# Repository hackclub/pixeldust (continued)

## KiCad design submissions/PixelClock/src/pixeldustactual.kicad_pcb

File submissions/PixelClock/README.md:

---
name: "Hudson Green"
slack_id: "U078RA454JH"
github_handle: "@PythonAtSea"
wokwi: https://wokwi.com/projects/429875870626598913
---

# pixelClock

[https://wokwi.com/projects/429875870626598913](https://wokwi.com/projects/429875870626598913)

⚠️ I would like to solder way more than 50 neopixels and a bunch of caps, so I would need a hotplate.

This is a grid of SK6821MINI leds. It is designed mainly to be used as a clock, but the surrounding leds could also be used for other things, and I'm planning on adding a alarm with a webpage later.

BOM

|   Comment     |   Footprint                                   |   Quantity    |   LCSC        |   Price   |
|---------------|-----------------------------------------------|---------------|---------------|-----------|
|   100nF       |   C_0201_0603Metric_Pad0.64x0.40mm_HandSolder |   133         |   C30926      |   $0.44   |
|   10uF        |   C_1210_3225Metric_Pad1.33x2.70mm_HandSolder |   1           |   C7432790    |   $0.38   |
|               |   XIAO-RP2040-DIP                             |   1		    |               |           |
|   Neopixel    |  	SK6812MINI                                  |   133		    |               |           |

Some images of your design (make sure to include both the PCB and Schematic!):

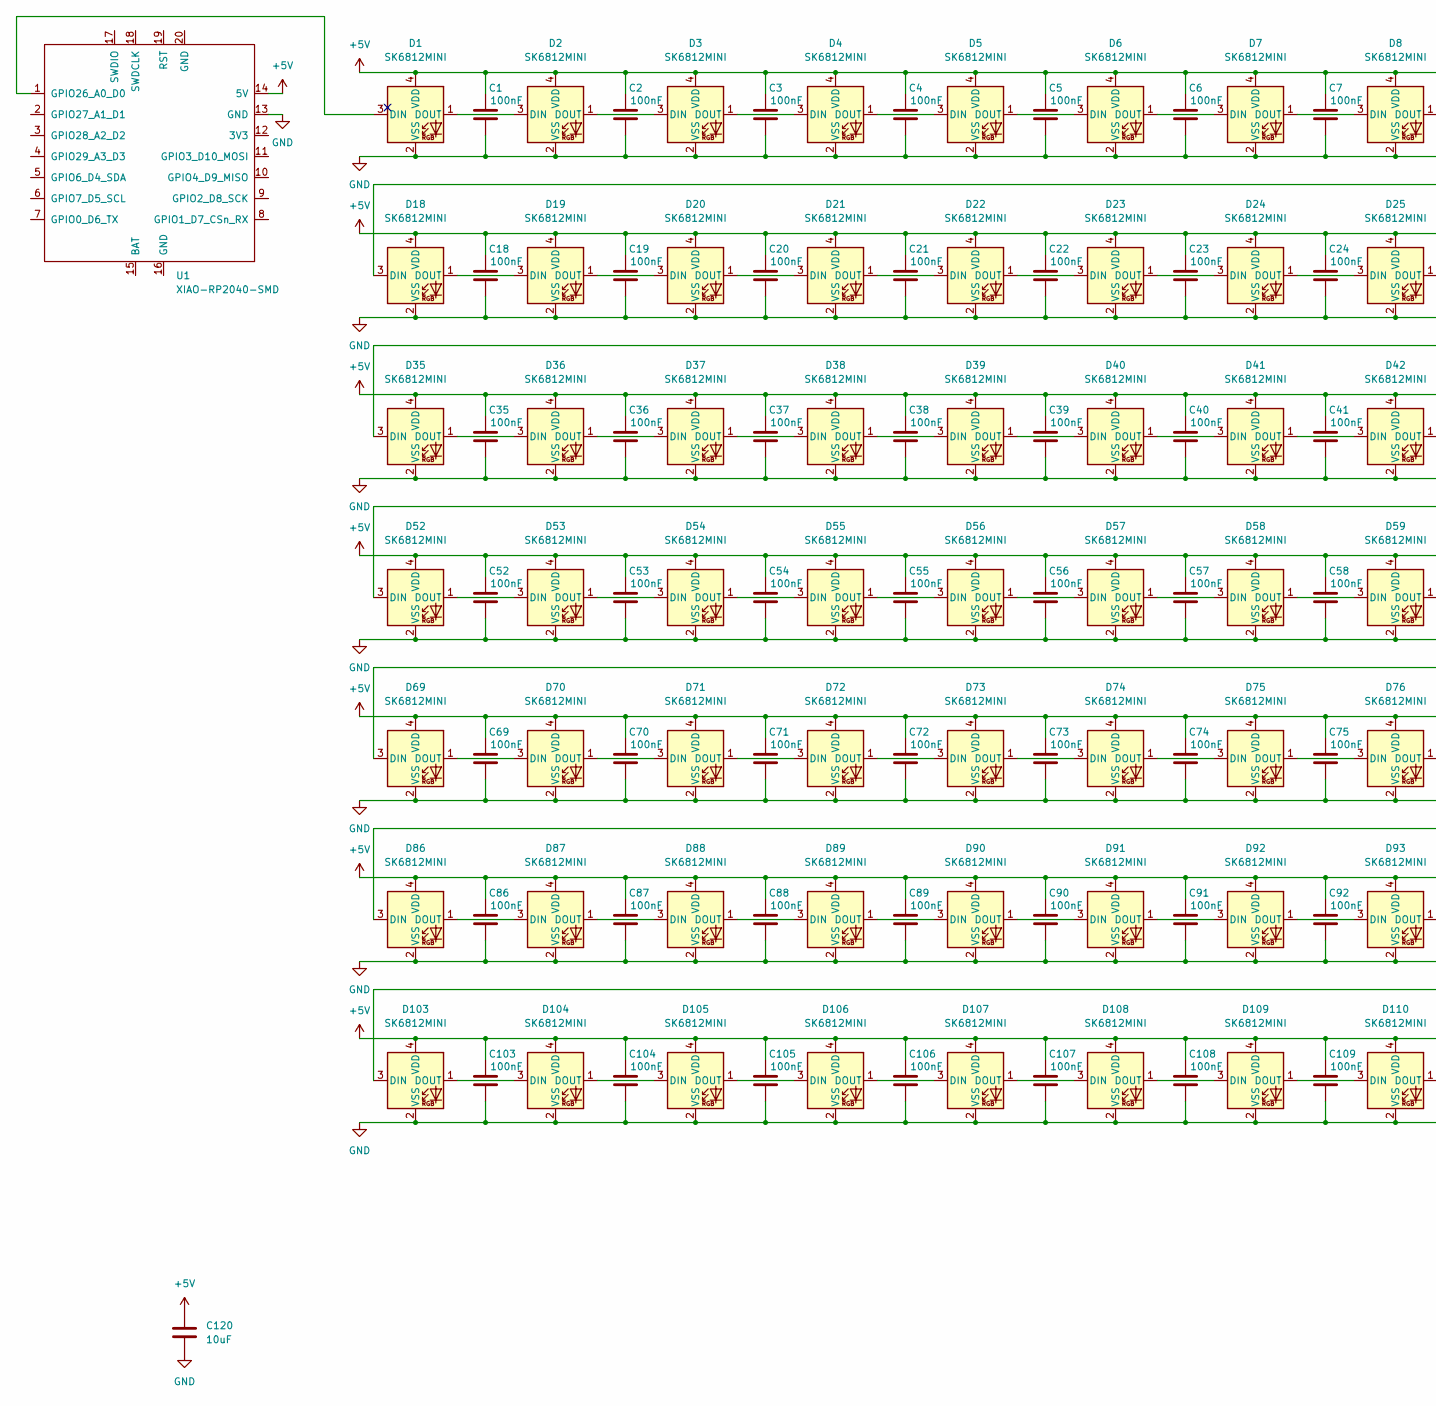
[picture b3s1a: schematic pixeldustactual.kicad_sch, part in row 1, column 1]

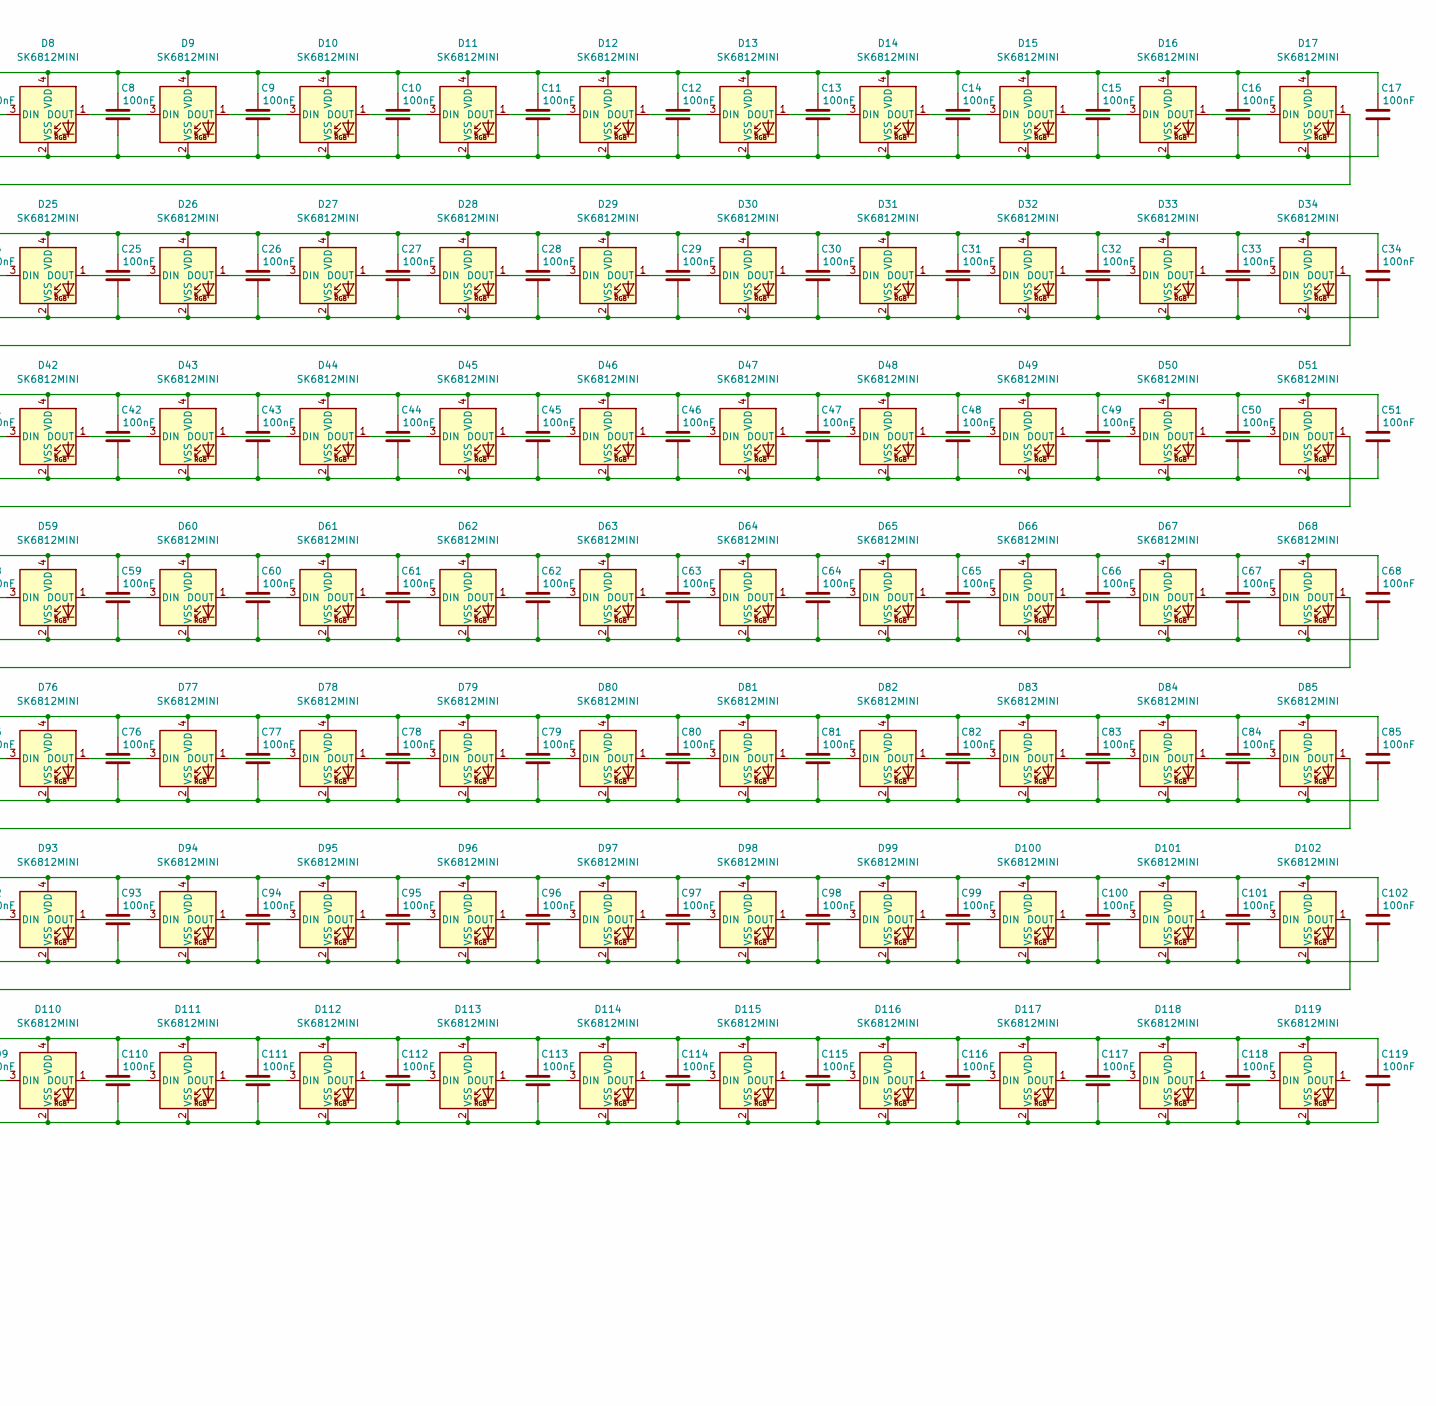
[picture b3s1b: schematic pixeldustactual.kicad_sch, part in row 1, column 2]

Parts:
C1, C2, C3, C4, C5, C6, C7, C8, C9, C10, C11, C12, C13, C14, C15, C16, C17, C18, C19, C20, C21, C22, C23, C24, C25, C26, C27, C28, C29, C30, C31, C32, C33, C34, C35, C36, C37, C38, C39, C40, C41, C42, C43, C44, C45, C46, C47, C48, C49, C50, C51, C52, C53, C54, C55, C56, C57, C58, C59, C60, C61, C62, C63, C64, C65, C66, C67, C68, C69, C70, C71, C72, C73, C74, C75, C76, C77, C78, C79, C80, C81, C82, C83, C84, C85, C86, C87, C88, C89, C90, C91, C92, C93, C94, C95, C96, C97, C98, C99, C100, C101, C102, C103, C104, C105, C106, C107, C108, C109, C110, C111, C112, C113, C114, C115, C116, C117, C118, C119: 100nF; C_0201_0603Metric_Pad0.64x0.40mm_HandSolder
C120: 10uF; C_1210_3225Metric_Pad1.33x2.70mm_HandSolder
D1, D2, D3, D4, D5, D6, D7, D8, D9, D10, D11, D12, D13, D14, D15, D16, D17, D18, D19, D20, D21, D22, D23, D24, D25, D26, D27, D28, D29, D30, D31, D32, D33, D34, D35, D36, D37, D38, D39, D40, D41, D42, D43, D44, D45, D46, D47, D48, D49, D50, D51, D52, D53, D54, D55, D56, D57, D58, D59, D60, D61, D62, D63, D64, D65, D66, D67, D68, D69, D70, D71, D72, D73, D74, D75, D76, D77, D78, D79, D80, D81, D82, D83, D84, D85, D86, D87, D88, D89, D90, D91, D92, D93, D94, D95, D96, D97, D98, D99, D100, D101, D102, D103, D104, D105, D106, D107, D108, D109, D110, D111, D112, D113, D114, D115, D116, D117, D118, D119: SK6812MINI; LED_SK6812MINI_PLCC4_3.5x3.5mm_P1.75mm
U1: XIAO-RP2040-SMD

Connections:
+5V: C1.1, C2.1, C3.1, C4.1, C5.1, C6.1, C7.1, C8.1, C9.1, C10.1, C11.1, C12.1, C13.1, C14.1, C15.1, C16.1, C17.1, C18.1, C19.1, C20.1, C21.1, C22.1, C23.1, C24.1, C25.1, C26.1, C27.1, C28.1, C29.1, C30.1, C31.1, C32.1, C33.1, C34.1, C35.1, C36.1, C37.1, C38.1, C39.1, C40.1, C41.1, C42.1, C43.1, C44.1, C45.1, C46.1, C47.1, C48.1, C49.1, C50.1, C51.1, C52.1, C53.1, C54.1, C55.1, C56.1, C57.1, C58.1, C59.1, C60.1, C61.1, C62.1, C63.1, C64.1, C65.1, C66.1, C67.1, C68.1, C69.1, C70.1, C71.1, C72.1, C73.1, C74.1, C75.1, C76.1, C77.1, C78.1, C79.1, C80.1, C81.1, C82.1, C83.1, C84.1, C85.1, C86.1, C87.1, C88.1, C89.1, C90.1, C91.1, C92.1, C93.1, C94.1, C95.1, C96.1, C97.1, C98.1, C99.1, C100.1, C101.1, C102.1, C103.1, C104.1, C105.1, C106.1, C107.1, C108.1, C109.1, C110.1, C111.1, C112.1, C113.1, C114.1, C115.1, C116.1, C117.1, C118.1, C119.1, C120.1, D1.4 (VDD), D2.4 (VDD), D3.4 (VDD), D4.4 (VDD), D5.4 (VDD), D6.4 (VDD), D7.4 (VDD), D8.4 (VDD), D9.4 (VDD), D10.4 (VDD), D11.4 (VDD), D12.4 (VDD), D13.4 (VDD), D14.4 (VDD), D15.4 (VDD), D16.4 (VDD), D17.4 (VDD), D18.4 (VDD), D19.4 (VDD), D20.4 (VDD), D21.4 (VDD), D22.4 (VDD), D23.4 (VDD), D24.4 (VDD), D25.4 (VDD), D26.4 (VDD), D27.4 (VDD), D28.4 (VDD), D29.4 (VDD), D30.4 (VDD), D31.4 (VDD), D32.4 (VDD), D33.4 (VDD), D34.4 (VDD), D35.4 (VDD), D36.4 (VDD), D37.4 (VDD), D38.4 (VDD), D39.4 (VDD), D40.4 (VDD), D41.4 (VDD), D42.4 (VDD), D43.4 (VDD), D44.4 (VDD), D45.4 (VDD), D46.4 (VDD), D47.4 (VDD), D48.4 (VDD), D49.4 (VDD), D50.4 (VDD), D51.4 (VDD), D52.4 (VDD), D53.4 (VDD), D54.4 (VDD), D55.4 (VDD), D56.4 (VDD), D57.4 (VDD), D58.4 (VDD), D59.4 (VDD), D60.4 (VDD), D61.4 (VDD), D62.4 (VDD), D63.4 (VDD), D64.4 (VDD), D65.4 (VDD), D66.4 (VDD), D67.4 (VDD), D68.4 (VDD), D69.4 (VDD), D70.4 (VDD), D71.4 (VDD), D72.4 (VDD), D73.4 (VDD), D74.4 (VDD), D75.4 (VDD), D76.4 (VDD), D77.4 (VDD), D78.4 (VDD), D79.4 (VDD), D80.4 (VDD), D81.4 (VDD), D82.4 (VDD), D83.4 (VDD), D84.4 (VDD), D85.4 (VDD), D86.4 (VDD), D87.4 (VDD), D88.4 (VDD), D89.4 (VDD), D90.4 (VDD), D91.4 (VDD), D92.4 (VDD), D93.4 (VDD), D94.4 (VDD), D95.4 (VDD), D96.4 (VDD), D97.4 (VDD), D98.4 (VDD), D99.4 (VDD), D100.4 (VDD), D101.4 (VDD), D102.4 (VDD), D103.4 (VDD), D104.4 (VDD), D105.4 (VDD), D106.4 (VDD), D107.4 (VDD), D108.4 (VDD), D109.4 (VDD), D110.4 (VDD), D111.4 (VDD), D112.4 (VDD), D113.4 (VDD), D114.4 (VDD), D115.4 (VDD), D116.4 (VDD), D117.4 (VDD), D118.4 (VDD), D119.4 (VDD), U1.14 (5V); also elsewhere on the board
GND: C1.2, C2.2, C3.2, C4.2, C5.2, C6.2, C7.2, C8.2, C9.2, C10.2, C11.2, C12.2, C13.2, C14.2, C15.2, C16.2, C17.2, C18.2, C19.2, C20.2, C21.2, C22.2, C23.2, C24.2, C25.2, C26.2, C27.2, C28.2, C29.2, C30.2, C31.2, C32.2, C33.2, C34.2, C35.2, C36.2, C37.2, C38.2, C39.2, C40.2, C41.2, C42.2, C43.2, C44.2, C45.2, C46.2, C47.2, C48.2, C49.2, C50.2, C51.2, C52.2, C53.2, C54.2, C55.2, C56.2, C57.2, C58.2, C59.2, C60.2, C61.2, C62.2, C63.2, C64.2, C65.2, C66.2, C67.2, C68.2, C69.2, C70.2, C71.2, C72.2, C73.2, C74.2, C75.2, C76.2, C77.2, C78.2, C79.2, C80.2, C81.2, C82.2, C83.2, C84.2, C85.2, C86.2, C87.2, C88.2, C89.2, C90.2, C91.2, C92.2, C93.2, C94.2, C95.2, C96.2, C97.2, C98.2, C99.2, C100.2, C101.2, C102.2, C103.2, C104.2, C105.2, C106.2, C107.2, C108.2, C109.2, C110.2, C111.2, C112.2, C113.2, C114.2, C115.2, C116.2, C117.2, C118.2, C119.2, C120.2, D1.2 (VSS), D2.2 (VSS), D3.2 (VSS), D4.2 (VSS), D5.2 (VSS), D6.2 (VSS), D7.2 (VSS), D8.2 (VSS), D9.2 (VSS), D10.2 (VSS), D11.2 (VSS), D12.2 (VSS), D13.2 (VSS), D14.2 (VSS), D15.2 (VSS), D16.2 (VSS), D17.2 (VSS), D18.2 (VSS), D19.2 (VSS), D20.2 (VSS), D21.2 (VSS), D22.2 (VSS), D23.2 (VSS), D24.2 (VSS), D25.2 (VSS), D26.2 (VSS), D27.2 (VSS), D28.2 (VSS), D29.2 (VSS), D30.2 (VSS), D31.2 (VSS), D32.2 (VSS), D33.2 (VSS), D34.2 (VSS), D35.2 (VSS), D36.2 (VSS), D37.2 (VSS), D38.2 (VSS), D39.2 (VSS), D40.2 (VSS), D41.2 (VSS), D42.2 (VSS), D43.2 (VSS), D44.2 (VSS), D45.2 (VSS), D46.2 (VSS), D47.2 (VSS), D48.2 (VSS), D49.2 (VSS), D50.2 (VSS), D51.2 (VSS), D52.2 (VSS), D53.2 (VSS), D54.2 (VSS), D55.2 (VSS), D56.2 (VSS), D57.2 (VSS), D58.2 (VSS), D59.2 (VSS), D60.2 (VSS), D61.2 (VSS), D62.2 (VSS), D63.2 (VSS), D64.2 (VSS), D65.2 (VSS), D66.2 (VSS), D67.2 (VSS), D68.2 (VSS), D69.2 (VSS), D70.2 (VSS), D71.2 (VSS), D72.2 (VSS), D73.2 (VSS), D74.2 (VSS), D75.2 (VSS), D76.2 (VSS), D77.2 (VSS), D78.2 (VSS), D79.2 (VSS), D80.2 (VSS), D81.2 (VSS), D82.2 (VSS), D83.2 (VSS), D84.2 (VSS), D85.2 (VSS), D86.2 (VSS), D87.2 (VSS), D88.2 (VSS), D89.2 (VSS), D90.2 (VSS), D91.2 (VSS), D92.2 (VSS), D93.2 (VSS), D94.2 (VSS), D95.2 (VSS), D96.2 (VSS), D97.2 (VSS), D98.2 (VSS), D99.2 (VSS), D100.2 (VSS), D101.2 (VSS), D102.2 (VSS), D103.2 (VSS), D104.2 (VSS), D105.2 (VSS), D106.2 (VSS), D107.2 (VSS), D108.2 (VSS), D109.2 (VSS), D110.2 (VSS), D111.2 (VSS), D112.2 (VSS), D113.2 (VSS), D114.2 (VSS), D115.2 (VSS), D116.2 (VSS), D117.2 (VSS), D118.2 (VSS), D119.2 (VSS), U1.13 (GND); also elsewhere on the board
unnamed: D1.1 (DOUT), D2.3 (DIN)
unnamed: D2.1 (DOUT), D3.3 (DIN)
unnamed: D3.1 (DOUT), D4.3 (DIN)
unnamed: D4.1 (DOUT), D5.3 (DIN)
unnamed: D5.1 (DOUT), D6.3 (DIN)
unnamed: D6.1 (DOUT), D7.3 (DIN)
unnamed: D7.1 (DOUT), D8.3 (DIN)
unnamed: D8.1 (DOUT), D9.3 (DIN)
unnamed: D9.1 (DOUT), D10.3 (DIN)
unnamed: D10.1 (DOUT), D11.3 (DIN)
unnamed: D11.1 (DOUT), D12.3 (DIN)
unnamed: D12.1 (DOUT), D13.3 (DIN)
unnamed: D13.1 (DOUT), D14.3 (DIN)
unnamed: D14.1 (DOUT), D15.3 (DIN)
unnamed: D15.1 (DOUT), D16.3 (DIN)
unnamed: D16.1 (DOUT), D17.3 (DIN)
unnamed: D17.1 (DOUT), D18.3 (DIN)
unnamed: D18.1 (DOUT), D19.3 (DIN)
unnamed: D19.1 (DOUT), D20.3 (DIN)
unnamed: D20.1 (DOUT), D21.3 (DIN)
unnamed: D21.1 (DOUT), D22.3 (DIN)
unnamed: D22.1 (DOUT), D23.3 (DIN)
unnamed: D23.1 (DOUT), D24.3 (DIN)
unnamed: D24.1 (DOUT), D25.3 (DIN)
unnamed: D25.1 (DOUT), D26.3 (DIN)
unnamed: D26.1 (DOUT), D27.3 (DIN)
unnamed: D27.1 (DOUT), D28.3 (DIN)
unnamed: D28.1 (DOUT), D29.3 (DIN)
unnamed: D29.1 (DOUT), D30.3 (DIN)
unnamed: D30.1 (DOUT), D31.3 (DIN)
unnamed: D31.1 (DOUT), D32.3 (DIN)
unnamed: D32.1 (DOUT), D33.3 (DIN)
unnamed: D33.1 (DOUT), D34.3 (DIN)
unnamed: D34.1 (DOUT), D35.3 (DIN)
unnamed: D35.1 (DOUT), D36.3 (DIN)
unnamed: D36.1 (DOUT), D37.3 (DIN)
unnamed: D37.1 (DOUT), D38.3 (DIN)
unnamed: D38.1 (DOUT), D39.3 (DIN)
unnamed: D39.1 (DOUT), D40.3 (DIN)
unnamed: D40.1 (DOUT), D41.3 (DIN)
unnamed: D41.1 (DOUT), D42.3 (DIN)
unnamed: D42.1 (DOUT), D43.3 (DIN)
unnamed: D43.1 (DOUT), D44.3 (DIN)
unnamed: D44.1 (DOUT), D45.3 (DIN)
unnamed: D45.1 (DOUT), D46.3 (DIN)
unnamed: D46.1 (DOUT), D47.3 (DIN)
unnamed: D47.1 (DOUT), D48.3 (DIN)
unnamed: D48.1 (DOUT), D49.3 (DIN)
unnamed: D49.1 (DOUT), D50.3 (DIN)
unnamed: D50.1 (DOUT), D51.3 (DIN)
unnamed: D51.1 (DOUT), D52.3 (DIN)
unnamed: D52.1 (DOUT), D53.3 (DIN)
unnamed: D53.1 (DOUT), D54.3 (DIN)
unnamed: D54.1 (DOUT), D55.3 (DIN)
unnamed: D55.1 (DOUT), D56.3 (DIN)
unnamed: D56.1 (DOUT), D57.3 (DIN)
unnamed: D57.1 (DOUT), D58.3 (DIN)
unnamed: D58.1 (DOUT), D59.3 (DIN)
unnamed: D59.1 (DOUT), D60.3 (DIN)
unnamed: D60.1 (DOUT), D61.3 (DIN)
unnamed: D61.1 (DOUT), D62.3 (DIN)
unnamed: D62.1 (DOUT), D63.3 (DIN)
unnamed: D63.1 (DOUT), D64.3 (DIN)
unnamed: D64.1 (DOUT), D65.3 (DIN)
unnamed: D65.1 (DOUT), D66.3 (DIN)
unnamed: D66.1 (DOUT), D67.3 (DIN)
unnamed: D67.1 (DOUT), D68.3 (DIN)
unnamed: D68.1 (DOUT), D69.3 (DIN)
unnamed: D69.1 (DOUT), D70.3 (DIN)
unnamed: D70.1 (DOUT), D71.3 (DIN)
unnamed: D71.1 (DOUT), D72.3 (DIN)
unnamed: D72.1 (DOUT), D73.3 (DIN)
unnamed: D73.1 (DOUT), D74.3 (DIN)
unnamed: D74.1 (DOUT), D75.3 (DIN)
unnamed: D75.1 (DOUT), D76.3 (DIN)
unnamed: D76.1 (DOUT), D77.3 (DIN)
unnamed: D77.1 (DOUT), D78.3 (DIN)
unnamed: D78.1 (DOUT), D79.3 (DIN)
unnamed: D79.1 (DOUT), D80.3 (DIN)
unnamed: D80.1 (DOUT), D81.3 (DIN)
unnamed: D81.1 (DOUT), D82.3 (DIN)
unnamed: D82.1 (DOUT), D83.3 (DIN)
unnamed: D83.1 (DOUT), D84.3 (DIN)
unnamed: D84.1 (DOUT), D85.3 (DIN)
unnamed: D85.1 (DOUT), D86.3 (DIN)
unnamed: D86.1 (DOUT), D87.3 (DIN)
unnamed: D87.1 (DOUT), D88.3 (DIN)
unnamed: D88.1 (DOUT), D89.3 (DIN)
unnamed: D89.1 (DOUT), D90.3 (DIN)
unnamed: D90.1 (DOUT), D91.3 (DIN)
unnamed: D91.1 (DOUT), D92.3 (DIN)
unnamed: D92.1 (DOUT), D93.3 (DIN)
unnamed: D93.1 (DOUT), D94.3 (DIN)
unnamed: D94.1 (DOUT), D95.3 (DIN)
unnamed: D95.1 (DOUT), D96.3 (DIN)
unnamed: D96.1 (DOUT), D97.3 (DIN)
unnamed: D97.1 (DOUT), D98.3 (DIN)
unnamed: D98.1 (DOUT), D99.3 (DIN)
unnamed: D99.1 (DOUT), D100.3 (DIN)
unnamed: D100.1 (DOUT), D101.3 (DIN)
unnamed: D101.1 (DOUT), D102.3 (DIN)
unnamed: D102.1 (DOUT), D103.3 (DIN)
unnamed: D103.1 (DOUT), D104.3 (DIN)
unnamed: D104.1 (DOUT), D105.3 (DIN)
unnamed: D105.1 (DOUT), D106.3 (DIN)
unnamed: D106.1 (DOUT), D107.3 (DIN)
unnamed: D107.1 (DOUT), D108.3 (DIN)
unnamed: D108.1 (DOUT), D109.3 (DIN)
unnamed: D109.1 (DOUT), D110.3 (DIN)
unnamed: D110.1 (DOUT), D111.3 (DIN)
unnamed: D111.1 (DOUT), D112.3 (DIN)
unnamed: D112.1 (DOUT), D113.3 (DIN)
unnamed: D113.1 (DOUT), D114.3 (DIN)
unnamed: D114.1 (DOUT), D115.3 (DIN)
unnamed: D115.1 (DOUT), D116.3 (DIN)
unnamed: D116.1 (DOUT), D117.3 (DIN)
unnamed: D117.1 (DOUT), D118.3 (DIN)
unnamed: D118.1 (DOUT), D119.3 (DIN)
unnamed 120: D119.1 (DOUT); also elsewhere on the board

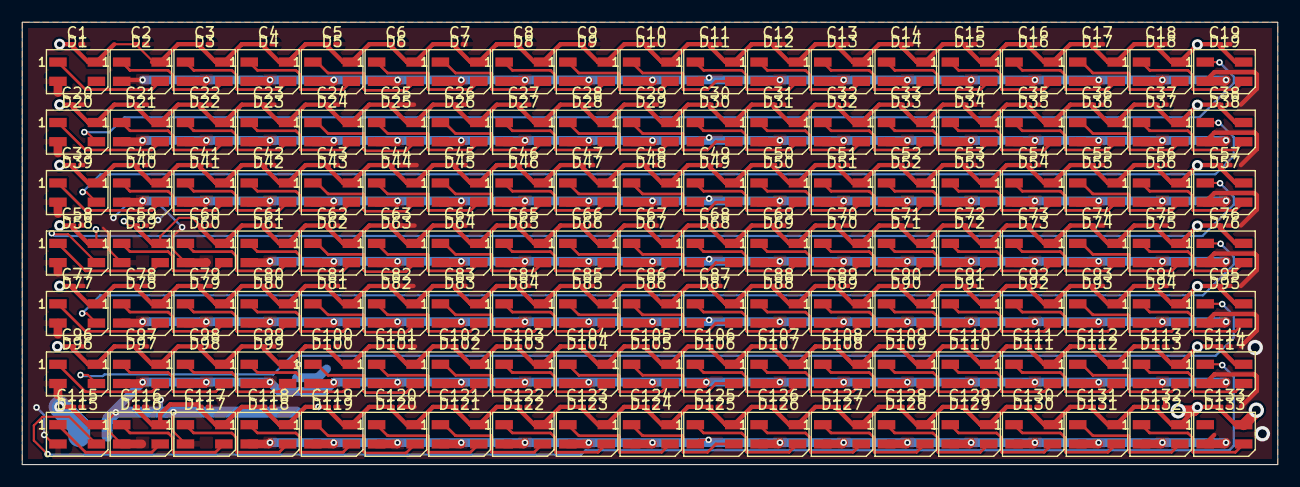
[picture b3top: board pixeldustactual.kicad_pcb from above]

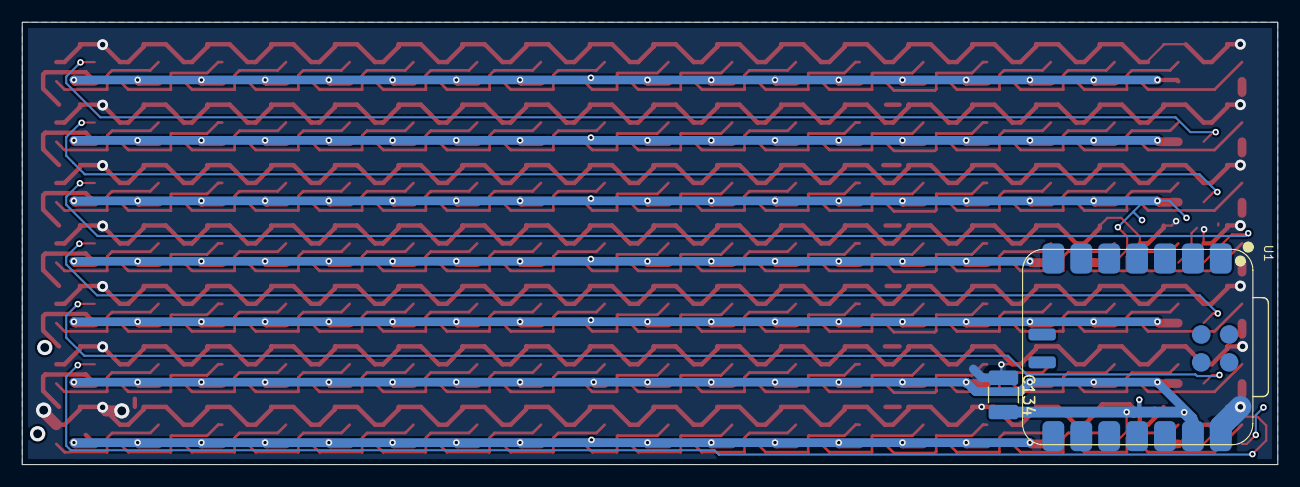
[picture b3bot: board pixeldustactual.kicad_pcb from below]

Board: 2 copper layers, 114.2 x 40.2 mm, 268 parts (2 on the bottom side), 134 nets.

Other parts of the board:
C121, C122, C123, C124, C125, C126, C127, C128, C129, C130, C131, C132, C133: 100nF; C_0201_0603Metric_Pad0.64x0.40mm_HandSolder
C134: 10uF; C_1210_3225Metric_Pad1.33x2.70mm_HandSolder
D120, D121, D122, D123, D124, D125, D126, D127, D128, D129, D130, D131, D132, D133: SK6812MINI; LED_SK6812MINI_PLCC4_3.5x3.5mm_P1.75mm

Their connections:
+5V: C121.1, C122.1, C123.1, C124.1, C125.1, C126.1, C127.1, C128.1, C129.1, C130.1, C131.1, C132.1, C133.1, C134.1, D120.4 (VDD), D121.4 (VDD), D122.4 (VDD), D123.4 (VDD), D124.4 (VDD), D125.4 (VDD), D126.4 (VDD), D127.4 (VDD), D128.4 (VDD), D129.4 (VDD), D130.4 (VDD), D131.4 (VDD), D132.4 (VDD), D133.4 (VDD); also elsewhere on the board
GND: C121.2, C122.2, C123.2, C124.2, C125.2, C126.2, C127.2, C128.2, C129.2, C130.2, C131.2, C132.2, C133.2, C134.2, D120.2 (VSS), D121.2 (VSS), D122.2 (VSS), D123.2 (VSS), D124.2 (VSS), D125.2 (VSS), D126.2 (VSS), D127.2 (VSS), D128.2 (VSS), D129.2 (VSS), D130.2 (VSS), D131.2 (VSS), D132.2 (VSS), D133.2 (VSS); also elsewhere on the board
unnamed 120: D120.3 (DIN); also elsewhere on the board
unnamed: D120.1 (DOUT), D121.3 (DIN)
unnamed: D121.1 (DOUT), D122.3 (DIN)
unnamed: D122.1 (DOUT), D123.3 (DIN)
unnamed: D123.1 (DOUT), D124.3 (DIN)
unnamed: D124.1 (DOUT), D125.3 (DIN)
unnamed: D125.1 (DOUT), D126.3 (DIN)
unnamed: D126.1 (DOUT), D127.3 (DIN)
unnamed: D127.1 (DOUT), D128.3 (DIN)
unnamed: D128.1 (DOUT), D129.3 (DIN)
unnamed: D129.1 (DOUT), D130.3 (DIN)
unnamed: D130.1 (DOUT), D131.3 (DIN)
unnamed: D131.1 (DOUT), D132.3 (DIN)
unnamed: D132.1 (DOUT), D133.3 (DIN)

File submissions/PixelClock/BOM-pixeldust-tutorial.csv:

Comment,Footprint,Quantity,LCSC,Price
100nF,C_0201_0603Metric_Pad0.64x0.40mm_HandSolder,133,C30926,$0.44 
10uF,C_0201_0603Metric_Pad0.64x0.40mm_HandSolder,1,C7432790,$0.38 
XIAO-RP2040-DIP,XIAO-RP2040-DIP,1,,
Neopixel,SK6812MINI,133,,
